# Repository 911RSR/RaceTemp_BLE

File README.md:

# RaceTemp_BLE

RaceTemp_BLE is an STM32WB55 based Bluetooth Low Energy sensor bridge for
RaceChrono. It reads local sensors, packages the measurements as RaceChrono
DIY CAN/BLE messages, and lets RaceChrono log them as if they came from a CAN
bus.

The project is based on the RaceChrono BLE DIY device idea from Aollin's demo
project:

https://github.com/aollin/racechrono-ble-diy-device

RaceTemp adds the temperature, pressure, thermocouple, RPM, engine-hours, and
engine-revolutions logic used by this project.

## Current Status

This is still a work in progress, but has som "track record" as it's 
the only logger we have used for track days and races in 2026.   

Implemented:

- BLE device name: `RaceTemp`
- RaceChrono-compatible CAN message characteristic
- Optional RaceChrono CAN filter handling
- ADC based MAP and NTC readings
- MAX31855 thermocouple support
- MAX31856 thermocouple support
- Ignition input based RPM measurement
- Engine operating hours counter
- Engine revolutions counter
- Persistent storage of engine counters after the engine stops
- Optional raw measurement snapshot message

## Building
You can download the binary (Release/RaceTemp_BLE.elf) and flash it to an STM32WB55. 
Android field flashing has been tested with STlinkP (Android app), STLINK-V3MINIE, 
and the WeAct STM32WB board. One can of course also flash it via ST-Link and 
STM32CubeProgrammer on a PC.   

If you want to compile yourself on a PC with STM32CubeMX and STM32CubeIDE, then follow this 4-step guide: 
1. Open the project in STM32CubeMX and click "GENERATE CODE".
This should generate some code files and copy some library files.
2. Run the script: .\tools\fix-cubemx-ble-duplicates.ps1
See also my CubeMX-notes at the bottom of this page.
3. Open the project in STM32CubeIDE and build the `Debug` or `Release` configuration.
4. Connect the STLink debug probe and flash the binary.  

The intended BLE security setup is:
- Bonding enabled
- No passkey
- No MITM requirement
- No input/output capability
- Secure connections mandatory
- GATT caching enabled
- Static random address `C0:52:54:42:4C:45`
- Advertisement includes the complete local name `RaceTemp`
- Advertisement includes the RaceChrono DIY service UUID `0x1ff8`

If pairing fails after a firmware or security setting change, delete/forget the
old `RaceTemp` pairing on the phone and pair again.

## Hardware Notes

Target MCU:

- STM32WB55CGU

The project has been developed and tested on a WeAct STM32WB55 board.

Thermocouple IC options:

- MAX31855
- MAX31856

The thermocouple IC is selected at compile time in:

```text
Core/Inc/RaceTemp_config.h
```

## Thermocouple Polarity

Do not trust wire color blindly. For many Type K thermocouples using US/ANSI
colors, yellow is positive and red is negative. Other color standards and probe
suppliers may differ.

A quick practical TC polarity check:

1. Connect the thermocouple.
2. Read the thermocouple channel in RaceChrono.
3. Warm the thermocouple tip with your fingers, hot air, or a lighter from a
   safe distance.
4. If the temperature goes up, the polarity is correct.
5. If the temperature goes down or becomes negative, swap the two thermocouple
   wires.

## Configuring The Thermocouple IC In Firmware

Edit `Core/Inc/RaceTemp_config.h` and set:

```c
#define RACETEMP_THERMOCOUPLE_IC RACETEMP_THERMOCOUPLE_IC_MAX31855
```

or:

```c
#define RACETEMP_THERMOCOUPLE_IC RACETEMP_THERMOCOUPLE_IC_MAX31856
```
For MAX31856, also select the thermocouple type. 
K-Type is most common (for motorsport and exhaust temperature). 

The firmware sends the thermocouple data as raw IC bytes on CAN ID `0x13`.
RaceChrono then decodes those bytes with an equation. This keeps the firmware
simple and makes it possible to inspect status and fault bits from the IC.

## Persistent Engine Counters

PID `21` / CAN ID `0x15` is the stored engine operating time in hours. It is a
lifetime counter, not time since boot. PID `22` / CAN ID `0x16` is the stored
engine revolution counter.

The counters are stored in the last two 4 KB flash pages:

- `0x0807E000`
- `0x0807F000`

The linker script reserves those pages by limiting normal application flash to
`504K`. This makes the firmware image fail to link before it can overlap the
counter storage.

Expected flashing behavior:

- Flashing with "erase necessary pages only" should preserve the counters.
- Flashing with mass erase / full chip erase resets the counters to zero.
- Manually erasing pages `0x0807E000` or `0x0807F000` resets the counters.

The firmware writes the counters to flash when RPM times out after the engine
stops. If the RPM input is left floating during bench testing, false pulses can
increase the counters, so keep the RPM input at a defined level when it is not
connected to a signal source.

## Using With RaceChrono

1. Power the RaceTemp device.
2. Pair the phone with the BLE device named `RaceTemp`.
3. Open RaceChrono.
4. Add/connect it as a RaceChrono BLE DIY/CAN device.
5. Add custom CAN channels for the CAN IDs listed below.
6. Enable the channels you want to log.

RaceChrono may show CAN IDs in either hexadecimal or decimal form. For example,
`0x13` is decimal `19`.

RaceChrono equations are documented here:

https://racechrono.com/support/equations

The thermocouple equations below use RaceChrono's `bitsToInt()` function. In
RaceChrono, bit offset 0 is the most significant bit of payload byte 0.
For the MAX31855 and MAX31856 temperature channels, the recommended equations
below use `bytesToInt()` because they are easier to enter correctly on a phone.

## RaceChrono CAN Channels

Most RaceTemp channels are sent as little-endian 32-bit floats. For those
channels, use this RaceChrono equation:

```text
bytesToFloatLe(raw, 0, 4)
```

| CAN ID | Decimal | Channel | Payload | Unit | RaceChrono equation |
| --- | ---: | --- | --- | --- | --- |
| `0x0B` | 11 | MAP pressure | float32 little-endian | kPa | `bytesToFloatLe(raw, 0, 4)` |
| `0x0C` | 12 | MAP NTC temperature | float32 little-endian | deg C | `bytesToFloatLe(raw, 0, 4)` |
| `0x0D` | 13 | Volvo NTC temperature | float32 little-endian | deg C | `bytesToFloatLe(raw, 0, 4)` |
| `0x0E` | 14 | AC NTC temperature | float32 little-endian | deg C | `bytesToFloatLe(raw, 0, 4)` |
| `0x0F` | 15 | KOSO NTC temperature | float32 little-endian | deg C | `bytesToFloatLe(raw, 0, 4)` |
| `0x10` | 16 | STM32 MCU temperature | float32 little-endian | deg C | `bytesToFloatLe(raw, 0, 4)` |
| `0x11` | 17 | MAP raw ADC value | float32 little-endian | ADC count | `bytesToFloatLe(raw, 0, 4)` |
| `0x12` | 18 | NTC raw ADC value | float32 little-endian | ADC count | `bytesToFloatLe(raw, 0, 4)` |
| `0x13` | 19 | Thermocouple raw data | IC-specific raw bytes | deg C | See thermocouple sections below |
| `0x14` | 20 | Engine speed | float32 little-endian | RPM | `bytesToFloatLe(raw, 0, 4)` |
| `0x15` | 21 | Engine operating time | float32 little-endian | hours | `bytesToFloatLe(raw, 0, 4)` |
| `0x16` | 22 | Engine revolutions | float32 little-endian | rev | `bytesToFloatLe(raw, 0, 4)` |
| `0x17` | 23 | Ignition period | float32 little-endian | timer ticks | `bytesToFloatLe(raw, 0, 4)` |
| `0x18` | 24 | Ignition captures | float32 little-endian | count | `bytesToFloatLe(raw, 0, 4)` |
| `0x19` | 25 | Ignition rejects | float32 little-endian | count | `bytesToFloatLe(raw, 0, 4)` |
| `0x1A` | 26 | EGT temperature | float32 little-endian | deg C | `bytesToFloatLe(raw, 0, 4)` |
| `0x1B` | 27 | Engine speed peak hold | float32 little-endian | RPM | `bytesToFloatLe(raw, 0, 4)` |
| `0x1C` | 28 | EGT peak hold | float32 little-endian | deg C | `bytesToFloatLe(raw, 0, 4)` |
| `0x1D` | 29 | Engine speed filtered | float32 little-endian | RPM | `bytesToFloatLe(raw, 0, 4)` |
| `0x1E` | 30 | Thermocouple status | float32 little-endian | bitmask | `bytesToFloatLe(raw, 0, 4)` |
| `0x1F` | 31 | Thermocouple recoveries | float32 little-endian | count | `bytesToFloatLe(raw, 0, 4)` |
| `0x20` | 32 | Raw measurement snapshot | packed raw bytes | debug | See source layout |
| `0x21` | 33 | RPM fast packet | packed float32 little-endian values | RPM | See RPM fast packet below |

The peak hold channels keep a new maximum value visible for 5 seconds. The RPM
peak hold uses the filtered RPM channel so single noisy periods do not create
false peaks. After 5 seconds without a higher sample, the held channels return
to the current live value.

The filtered RPM channel is calculated from a short recent ignition-period
window with outlier trimming. It is intended for the driver display. The raw RPM
channel remains useful for ignition pickup debugging.

## RPM Fast Packet

CAN ID `0x21` is sent at 25 Hz. It packs the driver-facing RPM values into one
BLE notification:

| Offset | Channel | Unit | RaceChrono equation |
| ---: | --- | --- | --- |
| 0 | RPM raw | RPM | `bytesToFloatLe(raw, 0, 4)` |
| 4 | RPM filtered | RPM | `bytesToFloatLe(raw, 4, 4)` |
| 8 | RPM peak hold | RPM | `bytesToFloatLe(raw, 8, 4)` |

The individual RPM and ignition debug channels remain available at the slower
sensor publishing rate for comparison and troubleshooting.

Thermocouple status is a bitmask:

- `1`: current EGT sample is valid
- `2`: SPI/read error
- `4`: thermocouple IC fault bit set
- `8`: MAX31856 config readback mismatch/error
- `16`: recovery was triggered on this sample
- `32`: implausible thermocouple temperature

When the thermocouple sample is invalid, the EGT channel sends `0 C`. This
is intentionally obvious in the driver display and logs; the firmware does not
hold the last good EGT value.

## Reading MAX31855 In RaceChrono

When `RACETEMP_THERMOCOUPLE_IC_MAX31855` is selected, CAN ID `0x13` contains
the four raw bytes read from the MAX31855. The byte order is the same as the IC
SPI transfer: most significant byte first.

The MAX31855 thermocouple temperature is a signed 14-bit value with
0.25 deg C per bit.

Recommended RaceChrono equation:

```text
bytesToInt(raw, 0, 2) / 16.0
```

Equivalent bitfield equation:

```text
bitsToInt(raw, 0, 14) * 0.25
```

The `bytesToInt()` version works because the MAX31855 thermocouple value is
left-aligned in the first two raw bytes.

Useful notes:

- The MAX31855 fault flag is bit D16 of the 32-bit raw value.
- The low bits contain the IC-specific fault details.
- A separate RaceChrono status channel can use `bytesToUint(raw, 3, 1)` to show
  the lowest raw byte.
- If the thermocouple channel shows unrealistic values, first confirm that the
  RaceTemp firmware is built for MAX31855 and not MAX31856.

## Reading MAX31856 In RaceChrono

When `RACETEMP_THERMOCOUPLE_IC_MAX31856` is selected, CAN ID `0x13` contains
four bytes:

| Payload byte | Contents |
| ---: | --- |
| 0 | MAX31856 `LTCBH` register |
| 1 | MAX31856 `LTCBM` register |
| 2 | MAX31856 `LTCBL` register |
| 3 | MAX31856 fault/status register |

The MAX31856 thermocouple temperature is a signed 19-bit value with
0.0078125 deg C per bit.

Recommended RaceChrono equation:

```text
bytesToInt(raw, 0, 3) / 4096.0
```

Equivalent bitfield equation:

```text
bitsToInt(raw, 0, 19) * 0.0078125
```

The `bytesToInt()` version works because the MAX31856 thermocouple value is
left-aligned in the first three raw bytes.

Useful notes:

- Select the correct thermocouple type in `RaceTemp_config.h`.
- Payload byte 3 is the MAX31856 fault/status register.
- A separate RaceChrono status channel can use `bytesToUint(raw, 3, 1)`.
- If the temperature is wrong but changes with heat, check the selected
  thermocouple type first.
- If the value is completely wrong, confirm that RaceChrono is using the
  MAX31856 equation and not the MAX31855 equation.

## Raw Measurement Snapshot

CAN ID `0x20` is intended for development and debugging. It sends one packed
snapshot of the raw measurement buffer:

- ADC samples
- Thermocouple SPI bytes
- Ignition timing data

Normal RaceChrono logging should usually use the individual channels instead.
The raw snapshot is useful when checking new sensors or debugging conversion
logic.

## Notes About CubeMX Regeneration

Unfortunately the current version of CubeMX can make some mistakes (it can duplicate user-section
content in the BLE files), and some generated files contain project-specific
settings. After regenerating the code, run the cleanup script before building:

```powershell
powershell -ExecutionPolicy Bypass -File .\tools\fix-cubemx-ble-duplicates.ps1
```

The script removes duplicate CubeMX generated BLE functions, restores the
RaceChrono BLE callbacks, restores the BLE security/address settings used by
this project, and repairs the local linker script.

Important local linker-script repairs:

- Normal application flash is limited to `504K`.
- `PERSIST` reserves the last two 4 KB flash pages for engine counters.
- `MAPPING_TABLE` is placed at `0x20030000`.
- `MB_MEM1` and `.MB_MEM2` are placed in the CPU2 shared RAMB area.
- `.MB_MEM2` is 4-byte aligned so startup initialization does not fault.

The script also removes the extra generated HSEM lock before `MX_APPE_Init()`.
Leaving that duplicate lock in place can stall BLE startup or lead to an early
HardFault.

To re-generate the code from CubeMX:

1. Open the .ioc file in CubeMX and click "GENERATE CODE"
2. Run `tools/fix-cubemx-ble-duplicates.ps1`
3. Build in STM32CubeIDE
4. Check that pairing still works with `RaceTemp`

Keep project-specific RaceTemp logic in the RaceTemp source files where
possible. This reduces the amount of code that lives inside CubeMX user
sections.

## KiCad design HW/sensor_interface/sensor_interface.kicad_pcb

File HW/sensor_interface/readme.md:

A sensor interface PCB designed and ordered on NiNo's 22 years birthday.  
The PCB has four inputs: 
1) RPM -- engine speed
2) EGT -- exhaust gas temperature
3) NTC1 -- water temperature 
4) NTC2 -- cylinder head temperature

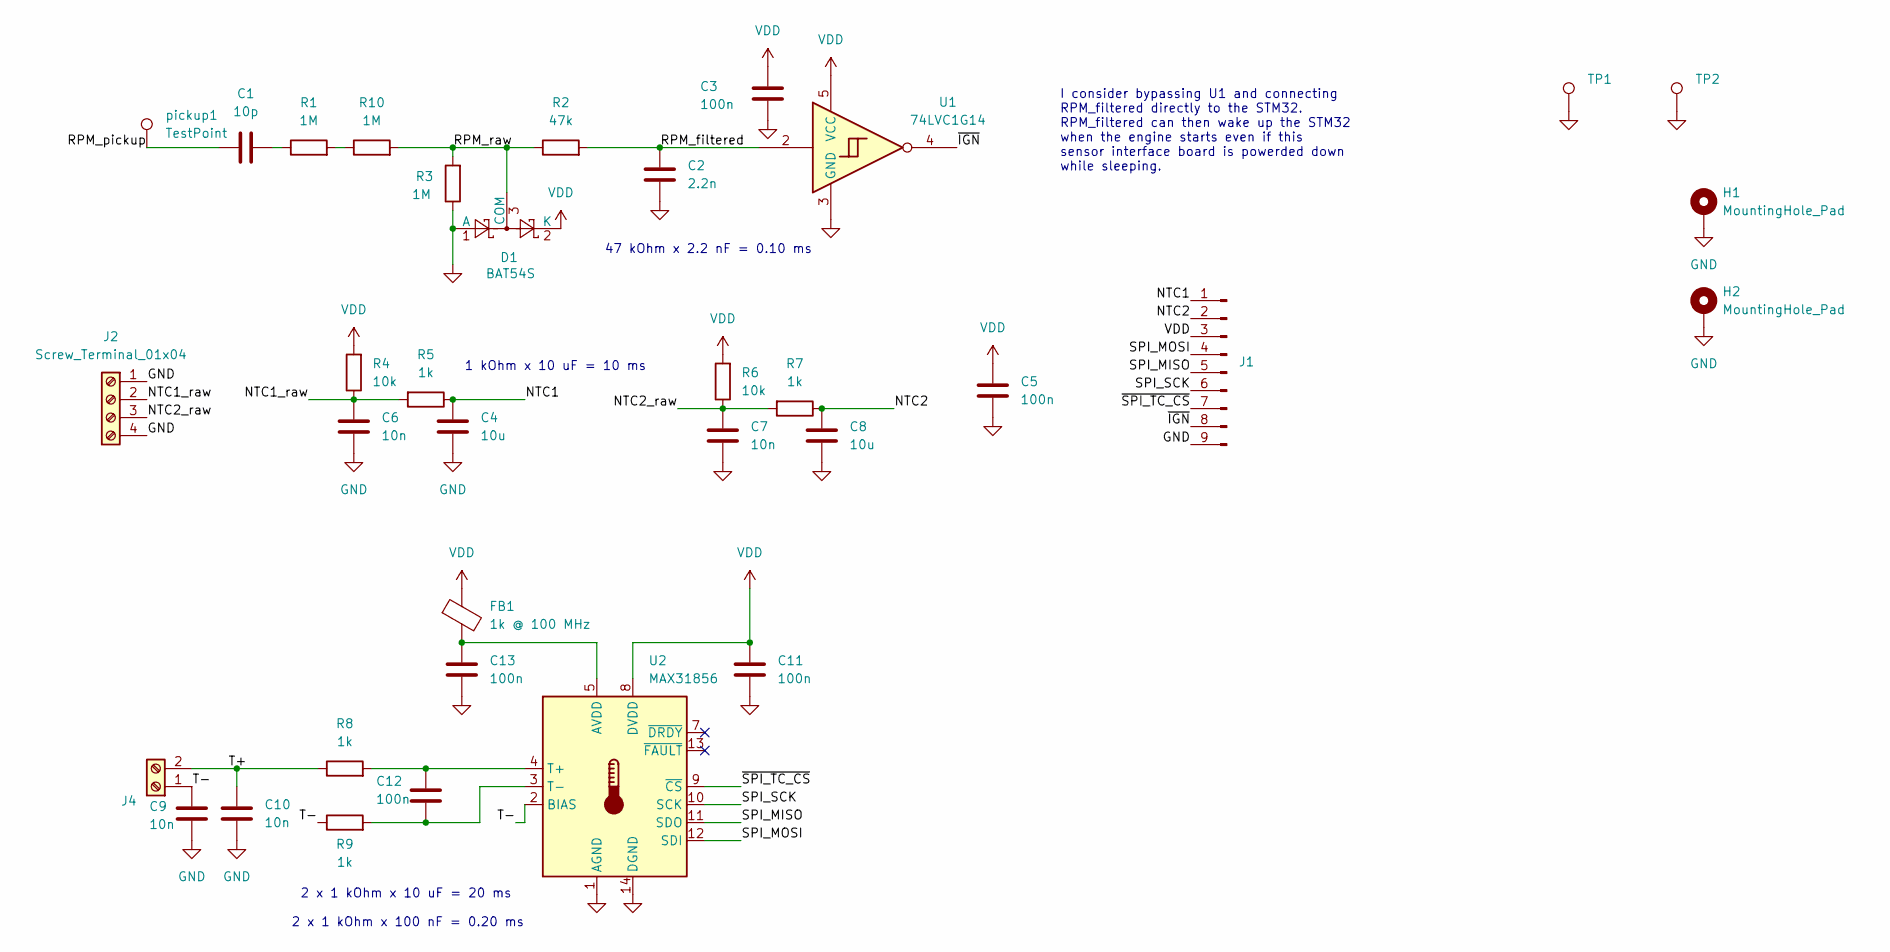
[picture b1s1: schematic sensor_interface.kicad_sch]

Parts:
C1: 10p; C_0805_2012Metric; MPN CC0805JRNPOCBN100
C2: 2.2n; C_0805_2012Metric; MPN C0805C222KAGECAUTO
C3, C5, C11, C12, C13: 100n; C_0805_2012Metric
C4, C8: 10u; C_0805_2012Metric
C6, C7, C9, C10: 10n; C_0805_2012Metric
D1: BAT54S; SOT-23; MPN BAT54S
FB1: 1k @ 100 MHz; R_0805_2012Metric
H1, H2: MountingHole_Pad; MountingHole_3.2mm_M3_Pad_Via
J1: Berg; PinHeader_1x09_P2.54mm_Vertical
J2: Screw_Terminal_01x04; TerminalBlock_Phoenix_MPT-0,5-4-2.54_1x04_P2.54mm_Horizontal
J4: Screw_Terminal; TerminalBlock_Phoenix_MPT-0,5-2-2.54_1x02_P2.54mm_Horizontal
R1: 1M; R_0805_2012Metric; MPN CRCW08051M00FKEA
R2: 47k; R_0805_2012Metric
R3, R10: 1M; R_0805_2012Metric
R4, R6: 10k; R_0805_2012Metric
R5, R7, R8, R9: 1k; R_0805_2012Metric
TP1, TP2: TestPoint; TestPoint_THTPad_4.0x4.0mm_Drill2.0mm
U1: 74LVC1G14; SOT-23-5_HandSoldering
U2: MAX31856; TSSOP-14_4.4x5mm_P0.65mm; MPN MAX31856MUD+T
pickup1: TestPoint; TestPoint_THTPad_D4.0mm_Drill2.0mm

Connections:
/NTC1: C4.2, J1.1, R5.1
/NTC1_raw: C6.2, J2.2, R4.1, R5.2
/NTC2: C8.2, J1.2, R7.1
/NTC2_raw: C7.2, J2.3, R6.1, R7.2
/RPM_filtered: C2.2, R2.2, U1.2
/RPM_pickup: C1.1, pickup1.1 (1_1)
/RPM_raw: D1.3 (COM), R2.1, R3.2, R10.2
/SPI_MISO: J1.5, U2.11 (SDO)
/SPI_MOSI: J1.4, U2.12 (SDI)
/SPI_SCK: J1.6, U2.10 (SCK)
/T+: C10.2, J4.2, R8.1
/T-: C9.2, J4.1, R9.1, U2.2 (BIAS)
/~IGN: J1.8, U1.4
/~SPI_TC_CS: J1.7, U2.9 (~CS)
GND: C2.1, C3.1, C4.1, C5.1, C6.1, C7.1, C8.1, C9.1, C10.1, C11.1, C13.1, D1.1 (A), H1.1 (1_1), H2.1 (1_1), J1.9, J2.1, J2.4, R3.1, TP1.1 (1_1), TP2.1 (1_1), U1.3 (GND), U2.1 (AGND), U2.14 (DGND)
unnamed: C1.2, R1.1
unnamed: R1.2, R10.1
unnamed: C13.2, FB1.2, U2.5 (AVDD)
unnamed: C12.2, R8.2, U2.4 (T+)
unnamed: C12.1, R9.2, U2.3 (T-)
VDD: C3.2, C5.2, C11.2, D1.2 (K), FB1.1, J1.3, R4.2, R6.2, U1.5 (VCC), U2.8 (DVDD)

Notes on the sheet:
2 x 1 kOhm x 10 uF = 20 ms
I consider bypassing U1 and connecting RPM_filtered directly to the STM32. RPM_filtered can then wake up the STM32 when the engine starts even if this sensor interface board is powerded down while sleeping.
47 kOhm x 2.2 nF = 0.10 ms
2 x 1 kOhm x 100 nF = 0.20 ms
1 kOhm x 10 uF = 10 ms

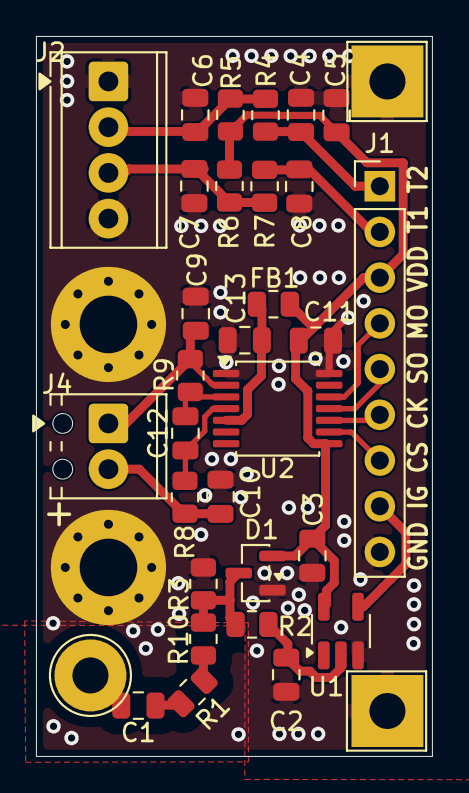
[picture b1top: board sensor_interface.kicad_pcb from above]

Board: 2 copper layers, 22.0 x 40.0 mm, 35 parts (0 on the bottom side), 21 nets.

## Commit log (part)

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2025-08-28 First check in. Too many files. The Makefile does not yet work, so compile via CubeIDE make system! Plan: Migrate from ST's UTIL_SEQ to FreeRTOS and merge with the main RaceTemp project.
2025-08-28 CTS (clear to send) for USART1. Makefile with correct startup.s and linker script. Added (and commented out) a Makefile rule for CubeMX code generation via command line interface and script.
2026-03-30 Add README content for RaceTemp_BLE
    Added detailed information about the BLE version of RaceTemp, including supported features, ADC connections, and CAN ID configurations.
2026-03-30 Fix README formatting and update MAX31855 references
    Updated README to correct references and improve clarity.
2026-03-30 Update README with compiling and usage instructions
    Added compilation instructions and usage details for RaceTemp_BLE.
2026-03-30 Fix formatting and add make command option in README
    make
2026-04-02 Revise README for project status and sensor support
    Updated README to clarify project status and features.
2026-04-02 Removed some auto-generated files from Git
2026-04-02 Fix formatting issues in README.md
2026-04-03 Should work with latest/current ST tools and libraries, but note:
    1: If it goes directly to HardFault_Handler(), then it might be a
    problem with shared RAM allocation in the auto generated FLASh.ld-file.
    I added a binary (Release/RaceTemp_BLE.elf.elf) which can be flashed
    with STM32CubeProgrammer. That binary is using an old FLASh.ld-file,
    and does not have that HardFault problem.
    2: I have only tested the binary with the BLE firmware
2026-05-15 Add files via upload
    A sensor interface PCB designed and ordered on NiNo's 22 years birthday.
    The PCB has four inputs:
    1) RPM -- engine speed
    2) EGT -- exhaust gas temperature
    3) NTC1 -- water temperature
    4) NTC2 -- cylinder head temperature
2026-05-17 code cleanup and prepare RPM input
2026-05-19 Remove personal RaceTemp repo leftovers
2026-05-26 Update readme with PCB images
    Added images of the front and back sides of the PCB to the readme.
2026-05-26 Improve formatting in sensor_interface readme
    Formatted the readme for better readability.
2026-05-27 Cleaned up text on F.Fab
2026-05-27 Update sensor_interface.kicad_sch
    Changed some capacitor and resistor values.
2026-05-27 Update sensor_interface.kicad_pcb
    Fixed a missing trace/connection to U2 pin 3.
2026-05-31 Restore working RaceTemp BLE pairing state
2026-05-31 fixed issue: kicad_pcb was not showing the PCB
2026-06-22 Add MAX31856 diagnostics and CJ calibration
2026-06-30 Update BLE pairing and sensor pull-ups
